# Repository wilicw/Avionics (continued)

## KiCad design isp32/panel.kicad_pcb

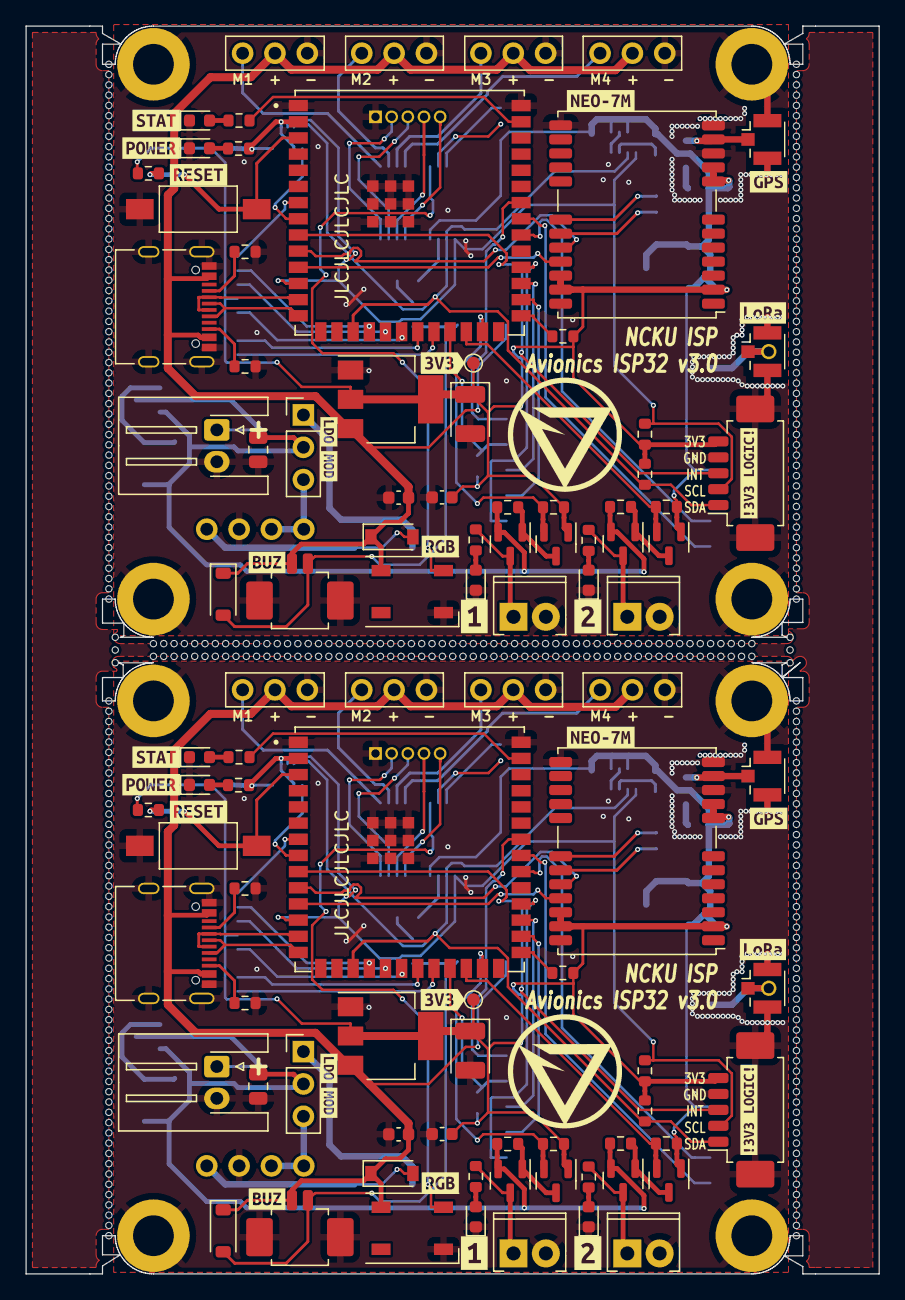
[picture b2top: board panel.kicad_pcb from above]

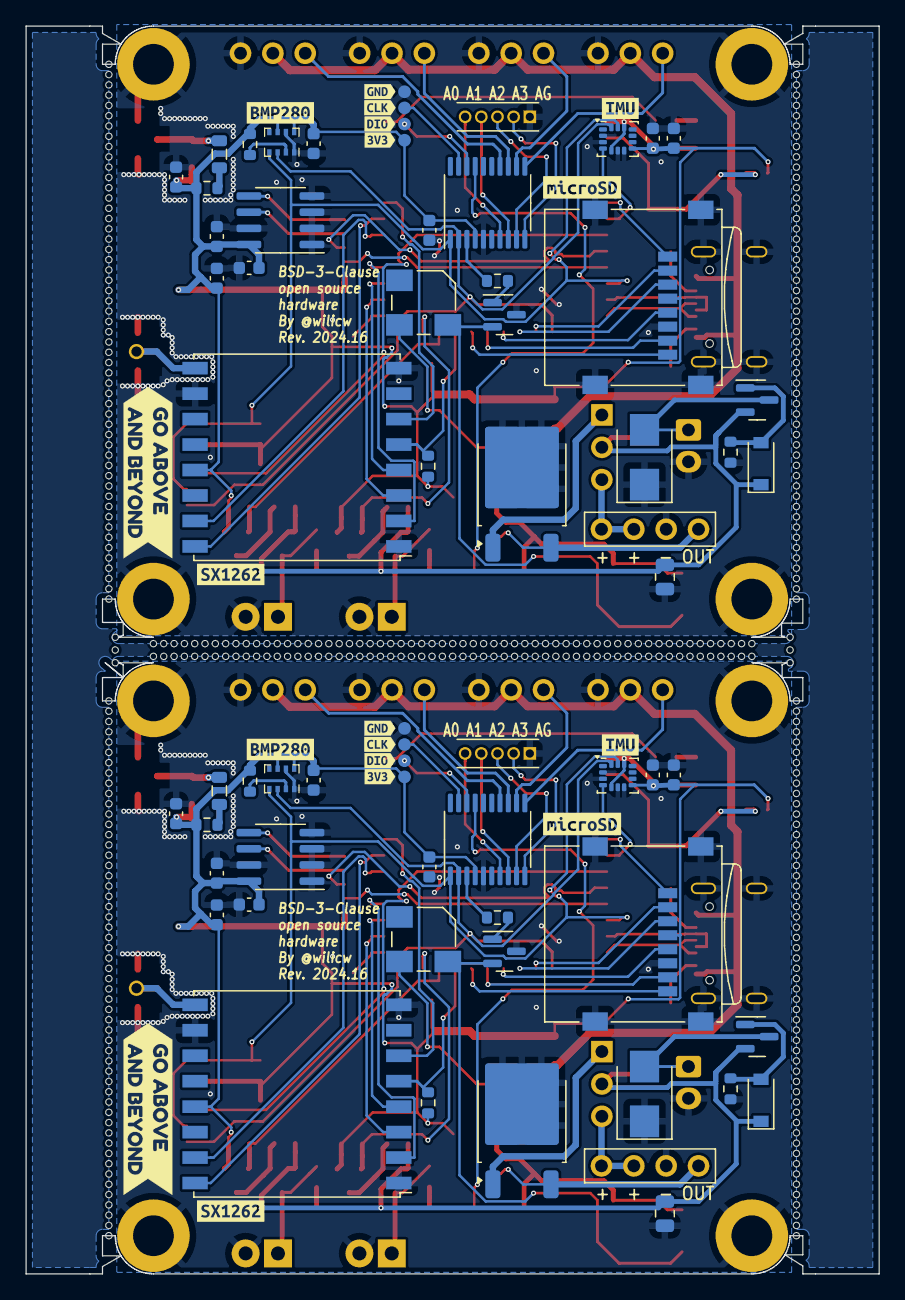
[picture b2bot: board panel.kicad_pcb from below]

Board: 2 copper layers, 67.0 x 98.0 mm, 552 parts (86 on the bottom side), 130 nets.

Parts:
C3, C3#2, C9, C9#2, C11, C11#2, C13, C13#2, C16, C16#2, C23, C23#2: 100n; C_0603_1608Metric
C5, C5#2: 100n; C_0805_2012Metric
C6, C6#2, C10, C10#2: 22u; C_0603_1608Metric
C12, C12#2: 220u; CP_EIA-3528-12_Kemet-T
C14, C14#2, C22, C22#2: 1u; C_0603_1608Metric
C15, C15#2: 10u; C_0805_2012Metric
D1, D1#2: Zener; D_SOD-123
D2, D2#2: F0_LED; LED_0603_1608Metric
D3, D3#2: ESP_LED; LED_0603_1608Metric
D4, D4#2: F1_LED; LED_0603_1608Metric
D5, D5#2: POWER; LED_0603_1608Metric
D6, D6#2: TVS; D_SMB
D7, D7#2: WS2812B; LED_WS2812B_PLCC4_5.0x5.0mm_P3.2mm
D8, D8#2: D_Shockley; D_SOD-123
D9, D9#2: D_Small; D_SOD-123
H1, H1#2, H2, H2#2, H3, H3#2, H4, H4#2: MountingHole_Pad; MountingHole_3.2mm_M3_ISO7380_Pad
J1, J1#2: BAT1; JST_XH_S2B-XH-A-1_1x02_P2.50mm_Horizontal
J2, J2#2: ExtBoard; Molex_PicoBlade_53261-0571_1x05-1MP_P1.25mm_Horizontal
J3, J3#2: USB_C_Receptacle_USB2.0; USB_C_Receptacle_Palconn_UTC16-G
J4, J4#2: ADC; PinHeader_1x05_P1.27mm_Vertical
J5, J5#2: GPS_ANT; U.FL_Hirose_U.FL-R-SMT-1_Vertical
J6, J6#2: F0; TerminalBlock_Phoenix_MPT-0,5-2-2.54_1x02_P2.54mm_Horizontal
J7, J7#2: F1; TerminalBlock_Phoenix_MPT-0,5-2-2.54_1x02_P2.54mm_Horizontal
J9, J9#2: ANT; PinHeader_1x01_P2.00mm_Vertical
J10, J10#2: LoRa_ANT; U.FL_Hirose_U.FL-R-SMT-1_Vertical
J11, J11#2: Power Modules; PinSocket_1x04_P2.54mm_Vertical
J12, J12#2: Micro_SD_Card; microSD_HC_Wuerth_693072010801
J13, J13#2: VIN_SELECT; PinHeader_1x03_P2.54mm_Vertical
J14, J14#2: BUZZ; Molex_PicoBlade_53261-0271_1x02-1MP_P1.25mm_Horizontal
KiKit_MB_1_1, KiKit_MB_1_2, KiKit_MB_1_3, KiKit_MB_1_4, KiKit_MB_1_5, KiKit_MB_1_6, KiKit_MB_1_7, KiKit_MB_1_8, KiKit_MB_1_9, KiKit_MB_1_10, KiKit_MB_1_11, KiKit_MB_1_12, KiKit_MB_1_13, KiKit_MB_1_14, KiKit_MB_1_15, KiKit_MB_1_16, KiKit_MB_1_17, KiKit_MB_1_18, KiKit_MB_1_19, KiKit_MB_1_20, KiKit_MB_1_21, KiKit_MB_1_22, KiKit_MB_1_23, KiKit_MB_1_24, KiKit_MB_1_25, KiKit_MB_1_26, KiKit_MB_1_27, KiKit_MB_1_28, KiKit_MB_1_29, KiKit_MB_1_30, KiKit_MB_1_31, KiKit_MB_1_32, KiKit_MB_1_33, KiKit_MB_1_34, KiKit_MB_1_35, KiKit_MB_1_36, KiKit_MB_1_37, KiKit_MB_1_38, KiKit_MB_1_39, KiKit_MB_1_40, KiKit_MB_1_41, KiKit_MB_1_42, KiKit_MB_1_43, KiKit_MB_1_44, KiKit_MB_1_45, KiKit_MB_1_46, KiKit_MB_1_47, KiKit_MB_1_48, KiKit_MB_1_49, KiKit_MB_1_50, KiKit_MB_1_51, KiKit_MB_1_52, KiKit_MB_1_53, KiKit_MB_2_1, KiKit_MB_2_2, KiKit_MB_2_3, KiKit_MB_2_4, KiKit_MB_2_5, KiKit_MB_2_6, KiKit_MB_2_7, KiKit_MB_2_8, KiKit_MB_2_9, KiKit_MB_2_10, KiKit_MB_2_11, KiKit_MB_2_12, KiKit_MB_2_13, KiKit_MB_2_14, KiKit_MB_2_15, KiKit_MB_2_16, KiKit_MB_2_17, KiKit_MB_2_18, KiKit_MB_2_19, KiKit_MB_2_20, KiKit_MB_2_21, KiKit_MB_2_22, KiKit_MB_2_23, KiKit_MB_2_24, KiKit_MB_2_25, KiKit_MB_2_26, KiKit_MB_2_27, KiKit_MB_2_28, KiKit_MB_2_29, KiKit_MB_2_30, KiKit_MB_2_31, KiKit_MB_2_32, KiKit_MB_2_33, KiKit_MB_2_34, KiKit_MB_2_35, KiKit_MB_2_36, KiKit_MB_2_37, KiKit_MB_2_38, KiKit_MB_2_39, KiKit_MB_2_40, KiKit_MB_2_41, KiKit_MB_2_42, KiKit_MB_2_43, KiKit_MB_2_44, KiKit_MB_2_45, KiKit_MB_2_46, KiKit_MB_2_47, KiKit_MB_2_48, KiKit_MB_2_49, KiKit_MB_2_50, KiKit_MB_2_51, KiKit_MB_2_52, KiKit_MB_2_53, KiKit_MB_2_54, KiKit_MB_2_55, KiKit_MB_2_56, KiKit_MB_2_57, KiKit_MB_2_58, KiKit_MB_2_59, KiKit_MB_3_1, KiKit_MB_3_2, KiKit_MB_3_3, KiKit_MB_3_4, KiKit_MB_3_5, KiKit_MB_3_6, KiKit_MB_3_7, KiKit_MB_3_8, KiKit_MB_3_9, KiKit_MB_3_10, KiKit_MB_3_11, KiKit_MB_3_12, KiKit_MB_3_13, KiKit_MB_3_14, KiKit_MB_3_15, KiKit_MB_3_16, KiKit_MB_3_17, KiKit_MB_3_18, KiKit_MB_3_19, KiKit_MB_3_20, KiKit_MB_3_21, KiKit_MB_3_22, KiKit_MB_3_23, KiKit_MB_3_24, KiKit_MB_3_25, KiKit_MB_3_26, KiKit_MB_3_27, KiKit_MB_3_28, KiKit_MB_3_29, KiKit_MB_3_30, KiKit_MB_3_31, KiKit_MB_3_32, KiKit_MB_3_33, KiKit_MB_3_34, KiKit_MB_3_35, KiKit_MB_3_36, KiKit_MB_3_37, KiKit_MB_3_38, KiKit_MB_3_39, KiKit_MB_3_40, KiKit_MB_3_41, KiKit_MB_3_42, KiKit_MB_3_43, KiKit_MB_3_44, KiKit_MB_3_45, KiKit_MB_3_46, KiKit_MB_3_47, KiKit_MB_3_48, KiKit_MB_3_49, KiKit_MB_3_50, KiKit_MB_3_51, KiKit_MB_3_52, KiKit_MB_3_53, KiKit_MB_4_1, KiKit_MB_4_2, KiKit_MB_4_3, KiKit_MB_4_4, KiKit_MB_4_5, KiKit_MB_4_6, KiKit_MB_4_7, KiKit_MB_4_8, KiKit_MB_4_9, KiKit_MB_4_10, KiKit_MB_4_11, KiKit_MB_4_12, KiKit_MB_4_13, KiKit_MB_4_14, KiKit_MB_4_15, KiKit_MB_4_16, KiKit_MB_4_17, KiKit_MB_4_18, KiKit_MB_4_19, KiKit_MB_4_20, KiKit_MB_4_21, KiKit_MB_4_22, KiKit_MB_4_23, KiKit_MB_4_24, KiKit_MB_4_25, KiKit_MB_4_26, KiKit_MB_4_27, KiKit_MB_4_28, KiKit_MB_4_29, KiKit_MB_4_30, KiKit_MB_4_31, KiKit_MB_4_32, KiKit_MB_4_33, KiKit_MB_4_34, KiKit_MB_4_35, KiKit_MB_4_36, KiKit_MB_4_37, KiKit_MB_4_38, KiKit_MB_4_39, KiKit_MB_4_40, KiKit_MB_4_41, KiKit_MB_4_42, KiKit_MB_4_43, KiKit_MB_4_44, KiKit_MB_4_45, KiKit_MB_4_46, KiKit_MB_4_47, KiKit_MB_4_48, KiKit_MB_4_49, KiKit_MB_4_50, KiKit_MB_4_51, KiKit_MB_4_52, KiKit_MB_4_53, KiKit_MB_5_1, KiKit_MB_5_2, KiKit_MB_5_3, KiKit_MB_5_4, KiKit_MB_5_5, KiKit_MB_5_6, KiKit_MB_5_7, KiKit_MB_5_8, KiKit_MB_5_9, KiKit_MB_5_10, KiKit_MB_5_11, KiKit_MB_5_12, KiKit_MB_5_13, KiKit_MB_5_14, KiKit_MB_5_15, KiKit_MB_5_16, KiKit_MB_5_17, KiKit_MB_5_18, KiKit_MB_5_19, KiKit_MB_5_20, KiKit_MB_5_21, KiKit_MB_5_22, KiKit_MB_5_23, KiKit_MB_5_24, KiKit_MB_5_25, KiKit_MB_5_26, KiKit_MB_5_27, KiKit_MB_5_28, KiKit_MB_5_29, KiKit_MB_5_30, KiKit_MB_5_31, KiKit_MB_5_32, KiKit_MB_5_33, KiKit_MB_5_34, KiKit_MB_5_35, KiKit_MB_5_36, KiKit_MB_5_37, KiKit_MB_5_38, KiKit_MB_5_39, KiKit_MB_5_40, KiKit_MB_5_41, KiKit_MB_5_42, KiKit_MB_5_43, KiKit_MB_5_44, KiKit_MB_5_45, KiKit_MB_5_46, KiKit_MB_5_47, KiKit_MB_5_48, KiKit_MB_5_49, KiKit_MB_5_50, KiKit_MB_5_51, KiKit_MB_5_52, KiKit_MB_5_53, KiKit_MB_5_54, KiKit_MB_5_55, KiKit_MB_5_56, KiKit_MB_5_57, KiKit_MB_5_58, KiKit_MB_5_59, KiKit_MB_6_1, KiKit_MB_6_2, KiKit_MB_6_3, KiKit_MB_6_4, KiKit_MB_6_5, KiKit_MB_6_6, KiKit_MB_6_7, KiKit_MB_6_8, KiKit_MB_6_9, KiKit_MB_6_10, KiKit_MB_6_11, KiKit_MB_6_12, KiKit_MB_6_13, KiKit_MB_6_14, KiKit_MB_6_15, KiKit_MB_6_16, KiKit_MB_6_17, KiKit_MB_6_18, KiKit_MB_6_19, KiKit_MB_6_20, KiKit_MB_6_21, KiKit_MB_6_22, KiKit_MB_6_23, KiKit_MB_6_24, KiKit_MB_6_25, KiKit_MB_6_26, KiKit_MB_6_27, KiKit_MB_6_28, KiKit_MB_6_29, KiKit_MB_6_30, KiKit_MB_6_31, KiKit_MB_6_32, KiKit_MB_6_33, KiKit_MB_6_34, KiKit_MB_6_35, KiKit_MB_6_36, KiKit_MB_6_37, KiKit_MB_6_38, KiKit_MB_6_39, KiKit_MB_6_40, KiKit_MB_6_41, KiKit_MB_6_42, KiKit_MB_6_43, KiKit_MB_6_44, KiKit_MB_6_45, KiKit_MB_6_46, KiKit_MB_6_47, KiKit_MB_6_48, KiKit_MB_6_49, KiKit_MB_6_50, KiKit_MB_6_51, KiKit_MB_6_52, KiKit_MB_6_53, KiKit_MB_7_1, KiKit_MB_7_2, KiKit_MB_7_3, KiKit_MB_8_1, KiKit_MB_8_2, KiKit_MB_8_3: NPTH
L2, L2#2: 22u; L_0805_2012Metric
LS1, LS1#2: 5020; XDCR_KSSG33J12-3
M1, M1#2, M2, M2#2, M3, M3#2, M4, M4#2: Motor_Servo; PinHeader_1x03_P2.54mm_Vertical
Q1, Q1#2, Q4, Q4#2: BSS138; SOT-23
Q2, Q2#2: S8050; SOT-23
Q3, Q3#2, Q5, Q5#2, Q6, Q6#2: IRLML6402; SOT-23
R1, R1#2, R2, R2#2, R14, R14#2, R15, R15#2, R22, R22#2, R25, R25#2: 10k; R_0603_1608Metric
R3, R3#2: 100; R_0603_1608Metric
R4, R4#2, R6, R6#2: 4k7; R_0603_1608Metric
R5, R5#2, R7, R7#2: 5k1; R_0603_1608Metric
R12, R12#2: 22; R_0603_1608Metric
R16, R16#2, R20, R20#2, R23, R23#2, R24, R24#2: 100K; R_0603_1608Metric
R18, R18#2, R19, R19#2: 1k; R_0603_1608Metric
R26, R26#2: 100k; R_0603_1608Metric
SW1, SW1#2: RST; SW_SPST_FSMSM
TP1, TP1#2: 3V3; TestPoint_Pad_D1.0mm
TP2, TP2#2: TP-3V3; TestPoint_Pad_D1.0mm
TP3, TP3#2: SWDIO; TestPoint_Pad_D1.0mm
TP4, TP4#2: SWCLK; TestPoint_Pad_D1.0mm
TP5, TP5#2: GND; TestPoint_Pad_D1.0mm
U1, U1#2: AZ1117-3.3; SOT-223-3_TabPin2
U2, U2#2: BA05C; TO-252-2
U3, U3#2: STM32G030F6; TSSOP-20_4.4x6.5mm_P0.65mm
U4, U4#2: LSM6DSM; LGA-14_3x2.5mm_P0.5mm_LayoutBorder3x4y
U6, U6#2: 24LC32; SOIC-8_3.9x4.9mm_P1.27mm
U7, U7#2: NEO-XM; ublox_NEO
U8, U8#2: ESP32-S3-WROOM-1U; XCVR_ESP32-S3-WROOM-1U
U9, U9#2: RFM98W-315S2; HOPERF_RFM9XW_SMD
U10, U10#2: BMP280; Bosch_LGA-8_2x2.5mm_P0.65mm_ClockwisePinNumbering
kibuzzard-63CD1E7F, kibuzzard-63CD1E7F#2: G***; kibuzzard-63CD1E7F
kibuzzard-63CD1E61, kibuzzard-63CD1E61#2: G***; kibuzzard-63CD1E61
kibuzzard-63CD1EC0, kibuzzard-63CD1EC0#2: G***; kibuzzard-63CD1EC0
kibuzzard-63CD1EC5, kibuzzard-63CD1EC5#2: G***; kibuzzard-63CD1EC5
kibuzzard-63CD04EB, kibuzzard-63CD04EB#2: G***; kibuzzard-63CD04EB
kibuzzard-63CD04FB, kibuzzard-63CD04FB#2: G***; kibuzzard-63CD04FB
kibuzzard-641A73AC, kibuzzard-641A73AC#2: G***; kibuzzard-641A73AC
kibuzzard-641A73E5, kibuzzard-641A73E5#2: G***; kibuzzard-641A73E5
kibuzzard-641A73FA, kibuzzard-641A73FA#2: G***; kibuzzard-641A73FA
kibuzzard-641A737F, kibuzzard-641A737F#2: G***; kibuzzard-641A737F
kibuzzard-641A7395, kibuzzard-641A7395#2: G***; kibuzzard-641A7395
kibuzzard-641A7704, kibuzzard-641A7704#2: G***; kibuzzard-641A7704
kibuzzard-642D97EE, kibuzzard-642D97EE#2: G***; kibuzzard-642D97EE
kibuzzard-661FABB5, kibuzzard-661FABB5#2: G***; kibuzzard-661FABB5
kibuzzard-661FAECF, kibuzzard-661FAECF#2: G***; kibuzzard-661FAECF
kibuzzard-661FBC0A, kibuzzard-661FBC0A#2: G***; kibuzzard-661FBC0A
kibuzzard-661FBC21, kibuzzard-661FBC21#2: G***; kibuzzard-661FBC21
kibuzzard-66439A83, kibuzzard-66439A83#2: G***; kibuzzard-66439A83
kibuzzard-66439ACD, kibuzzard-66439ACD#2: G***; kibuzzard-66439ACD
kibuzzard-66439AF0, kibuzzard-66439AF0#2: G***; kibuzzard-66439AF0
kibuzzard-66439B8F, kibuzzard-66439B8F#2: G***; kibuzzard-66439B8F
kibuzzard-66439B33, kibuzzard-66439B33#2: G***; kibuzzard-66439B33
kibuzzard-66439C31, kibuzzard-66439C31#2: G***; kibuzzard-66439C31

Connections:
Board_0-+3V3: C3#2.1, C9.1, C10#2.1, C11.1, C12#2.1, C13#2.1, C14.1, C16.1, C22#2.1, C23.1, J2#2.5, J12#2.4 (VDD), Q1#2.1 (G), Q4#2.1 (G), R1.1, R2#2.1, R4#2.1, R6.1, R12.1, R14#2.1, R15.1, R16#2.1, R18#2.1, R23#2.1, TP1#2.1, TP2#2.1, U1#2.2 (VO), U3#2.4 (VDD), U4#2.5 (VDDIO), U4#2.8 (VDD), U4#2.12 (CS), U6.8 (VCC), U7.2 (D_SEL), U7.8 (~RESET), U7.9 (VCC_RF), U7.22 (V_BCKP), U7.23 (VCC), U8.2 (3V3), U9#2.13 (3.3V), U10#2.6 (VDDIO), U10#2.8 (VDD)
Board_0-+5V: C6.1, D7.1 (VDD), D8.1 (K), D9.1 (K), J3#2.A4 (VBUS), J3#2.A9 (VBUS), J3#2.B4 (VBUS), J3#2.B9 (VBUS), J14.1, LS1#2.P, M1#2.2 (+), M2#2.2 (+), M3#2.2 (+), M4.2 (+), U1#2.3 (VI)
Board_0-+BATT: C5.1, C15#2.1, D1.1 (K), J13#2.2, Q3.2 (S), Q5.2 (S), Q6#2.2 (S), R20#2.1, R24#2.1
Board_0-ADC0: J4#2.1, U3#2.7 (PA0)
Board_0-ADC1: J4#2.2, U3#2.8 (PA1)
Board_0-ADC2: J4#2.3, U3#2.9 (PA2)
Board_0-ADC3: J4#2.4, U3#2.10 (PA3)
Board_0-Buzz: R3#2.1, U3#2.3 (PC15-OSC32_OUT)
Board_0-D+: J3#2.A6 (D+), J3#2.B6 (D+), U8.14 (IO20)
Board_0-D-: J3#2.A7 (D-), J3#2.B7 (D-), U8.13 (IO19)
Board_0-EXT_INT: J2#2.3, U8.9 (IO16)
Board_0-FIRE0: Q1#2.2 (S), R16#2.2, U8.24 (IO47)
Board_0-FIRE1: Q4#2.2 (S), R23#2.2, U8.25 (IO48)
Board_0-GND: C3#2.2, C5.2, C6.2, C9.2, C10#2.2, C11.2, C12#2.2, C13#2.2, C14.2, C15#2.2, C16.2, C22#2.2, C23.2, D2.1 (K), D3#2.1 (K), D4#2.1 (K), D5.1 (K), D6#2.1 (A1), D7.3 (VSS), H1#2.1, H2.1, H3#2.1, H4#2.1, J1#2.2, J2#2.4, J2#2.MP (MountPin), J3#2.A1 (GND), J3#2.A12 (GND), J3#2.B1 (GND), J3#2.B12 (GND), J3#2.S1 (SHIELD), J4#2.5, J5.2 (Ext), J6.2, J7.2, J10.2 (Ext), J11.2, J12#2.6 (VSS), J12#2.9 (SHIELD), J14.MP (MountPin), M1#2.3 (-), M2#2.3 (-), M3#2.3 (-), M4.3 (-), Q2#2.3 (E), R5.2, R7.2, R26.2, SW1.1, TP5#2.1, U1#2.1 (GND), U2#2.2 (GND), U3#2.5 (VSS), U4#2.2 (SDX), U4#2.3 (SCX), U4#2.6 (GND), U4#2.7 (GND), U6.1 (A0), U6.2 (A1), U6.3 (A2), U6.4 (GND), U6.7 (WP), U7.10 (GND), U7.12 (GND), U7.13 (GND), U7.24 (GND), U8.1 (GND), U8.40 (GND), U8.41_1 (GND), U8.41_2 (GND), U8.41_3 (GND), U8.41_4 (GND), U8.41_5 (GND), U8.41_6 (GND), U8.41_7 (GND), U8.41_8 (GND), U8.41_9 (GND), U9#2.1 (GND), U9#2.8 (GND), U9#2.10 (GND), U10#2.1 (GND), U10#2.7 (GND)
Board_0-IMU_INT: U4#2.4 (INT1), U8.8 (IO15)
Board_0-INDI: R19.1, U8.39 (IO1)
Board_0-IO0: R2#2.2, U8.27 (IO0)
Board_0-LORA_BUSY: U8.33 (IO40), U9#2.16 (DIO2)
Board_0-LORA_D1: U8.32 (IO39), U9#2.15 (DIO1)
Board_0-LORA_RST: U8.34 (IO41), U9#2.6 (RESET)
Board_0-LORA_SS: R15.2, U8.23 (IO21), U9#2.5 (NSS)
Board_0-MISO_1: U8.30 (IO37), U9#2.2 (MISO)
Board_0-MOSI_1: U8.28 (IO35), U9#2.3 (MOSI)
Board_0-Net-(D1-A): D1.2 (A), Q6#2.1 (G), R26.1
Board_0-Net-(D2-A): D2.2 (A), R22#2.1
Board_0-Net-(D3-A): D3#2.2 (A), R19.2
Board_0-Net-(D4-A): D4#2.2 (A), R25#2.1
Board_0-Net-(D5-A): D5.2 (A), R18#2.2
Board_0-Net-(D6-A2): D6#2.2 (A2), J1#2.1, Q6#2.3 (D)
Board_0-Net-(D8-A): D8.2 (A), J11.1, U2#2.3 (VOUT)
Board_0-Net-(D9-A): D9.2 (A), J14.2, LS1#2.N, Q2#2.2 (C)
Board_0-Net-(J5-In): J5.1 (In), L2#2.2, U7.11 (RF_IN)
Board_0-Net-(J6-Pin_1): J6.1, Q3.3 (D), R22#2.2
Board_0-Net-(J7-Pin_1): J7.1, Q5.3 (D), R25#2.2
Board_0-Net-(J10-In): J9#2.1, J10.1 (In), U9#2.9 (ANT)
Board_0-Net-(J11-Pin_3): J11.3, J11.4, J13#2.3
Board_0-Net-(J13-Pin_1): J13#2.1, U2#2.1 (VIN)
Board_0-Net-(L2-Pad1): L2#2.1, R12.2
Board_0-Net-(Q1-D): Q1#2.3 (D), Q3.1 (G), R20#2.2
Board_0-Net-(Q2-B): Q2#2.1 (B), R3#2.2
Board_0-Net-(Q4-D): Q4#2.3 (D), Q5.1 (G), R24#2.2
Board_0-Net-(U6-SCL): U6.6 (SCL), U7.19 (SCL/SPI_CLK)
Board_0-Net-(U6-SDA): U6.5 (SDA), U7.18 (SDA/~SPI_CS)
Board_0-Net-(U10-CSB): R14#2.2, U10#2.2 (CSB)
Board_0-RGB: D7.4 (DIN), U3#2.17 (PA12[PA10])
Board_0-RST: R1.2, SW1.2, U8.3 (EN)
Board_0-RX1: U7.20 (TXD/SPI_MISO), U8.10 (IO17)
Board_0-SCK_1: U8.29 (IO36), U9#2.4 (SCK)
Board_0-SCL: J2#2.2, R6.2, U3#2.1 (PB7/PB8), U4#2.13 (SCL), U8.12 (IO8), U10#2.4 (SCK)
Board_0-SDA: J2#2.1, R4#2.2, U3#2.2 (PB9/PC14-OSC32_IN), U4#2.14 (SDA), U8.17 (IO9), U10#2.3 (SDI)
Board_0-SD_CLK: J12#2.5 (CLK), U8.20 (IO12)
Board_0-SD_CMD: J12#2.3 (CMD), U8.19 (IO11)
Board_0-SD_D0: J12#2.7 (DAT0), U8.21 (IO13)
Board_0-SD_D1: J12#2.8 (DAT1), U8.22 (IO14)
Board_0-SD_D2: J12#2.1 (DAT2), U8.7 (IO7)
Board_0-SD_D3: J12#2.2 (DAT3/CD), U8.18 (IO10)
Board_0-SERVO0: M1#2.1 (PWM), U3#2.11 (PA4)
Board_0-SERVO1: M2#2.1 (PWM), U3#2.12 (PA5)
Board_0-SERVO2: M3#2.1 (PWM), U3#2.13 (PA6)
Board_0-SERVO3: M4.1 (PWM), U3#2.14 (PA7)
Board_0-SWCLK: TP4#2.1, U3#2.19 (PA15/PA14-BOOT0)
Board_0-SWDIO: TP3#2.1, U3#2.18 (PA13)
Board_0-TX1: U7.21 (RXD/SPI_MOSI), U8.11 (IO18)
Board_0-cc1: J3#2.A5 (CC1), R5.1
Board_0-cc2: J3#2.B5 (CC2), R7.1
Board_1-+3V3: C3.1, C9#2.1, C10.1, C11#2.1, C12.1, C13.1, C14#2.1, C16#2.1, C22.1, C23#2.1, J2.5, J12.4 (VDD), Q1.1 (G), Q4.1 (G), R1#2.1, R2.1, R4.1, R6#2.1, R12#2.1, R14.1, R15#2.1, R16.1, R18.1, R23.1, TP1.1, TP2.1, U1.2 (VO), U3.4 (VDD), U4.5 (VDDIO), U4.8 (VDD), U4.12 (CS), U6#2.8 (VCC), U7#2.2 (D_SEL), U7#2.8 (~RESET), U7#2.9 (VCC_RF), U7#2.22 (V_BCKP), U7#2.23 (VCC), U8#2.2 (3V3), U9.13 (3.3V), U10.6 (VDDIO), U10.8 (VDD)
Board_1-+5V: C6#2.1, D7#2.1 (VDD), D8#2.1 (K), D9#2.1 (K), J3.A4 (VBUS), J3.A9 (VBUS), J3.B4 (VBUS), J3.B9 (VBUS), J14#2.1, LS1.P, M1.2 (+), M2.2 (+), M3.2 (+), M4#2.2 (+), U1.3 (VI)
Board_1-+BATT: C5#2.1, C15.1, D1#2.1 (K), J13.2, Q3#2.2 (S), Q5#2.2 (S), Q6.2 (S), R20.1, R24.1
Board_1-ADC0: J4.1, U3.7 (PA0)
Board_1-ADC1: J4.2, U3.8 (PA1)
Board_1-ADC2: J4.3, U3.9 (PA2)
Board_1-ADC3: J4.4, U3.10 (PA3)
Board_1-Buzz: R3.1, U3.3 (PC15-OSC32_OUT)
Board_1-D+: J3.A6 (D+), J3.B6 (D+), U8#2.14 (IO20)
Board_1-D-: J3.A7 (D-), J3.B7 (D-), U8#2.13 (IO19)
Board_1-EXT_INT: J2.3, U8#2.9 (IO16)
Board_1-FIRE0: Q1.2 (S), R16.2, U8#2.24 (IO47)
Board_1-FIRE1: Q4.2 (S), R23.2, U8#2.25 (IO48)
Board_1-GND: C3.2, C5#2.2, C6#2.2, C9#2.2, C10.2, C11#2.2, C12.2, C13.2, C14#2.2, C15.2, C16#2.2, C22.2, C23#2.2, D2#2.1 (K), D3.1 (K), D4.1 (K), D5#2.1 (K), D6.1 (A1), D7#2.3 (VSS), H1.1, H2#2.1, H3.1, H4.1, J1.2, J2.4, J2.MP (MountPin), J3.A1 (GND), J3.A12 (GND), J3.B1 (GND), J3.B12 (GND), J3.S1 (SHIELD), J4.5, J5#2.2 (Ext), J6#2.2, J7#2.2, J10#2.2 (Ext), J11#2.2, J12.6 (VSS), J12.9 (SHIELD), J14#2.MP (MountPin), M1.3 (-), M2.3 (-), M3.3 (-), M4#2.3 (-), Q2.3 (E), R5#2.2, R7#2.2, R26#2.2, SW1#2.1, TP5.1, U1.1 (GND), U2.2 (GND), U3.5 (VSS), U4.2 (SDX), U4.3 (SCX), U4.6 (GND), U4.7 (GND), U6#2.1 (A0), U6#2.2 (A1), U6#2.3 (A2), U6#2.4 (GND), U6#2.7 (WP), U7#2.10 (GND), U7#2.12 (GND), U7#2.13 (GND), U7#2.24 (GND), U8#2.1 (GND), U8#2.40 (GND), U8#2.41_1 (GND), U8#2.41_2 (GND), U8#2.41_3 (GND), U8#2.41_4 (GND), U8#2.41_5 (GND), U8#2.41_6 (GND), U8#2.41_7 (GND), U8#2.41_8 (GND), U8#2.41_9 (GND), U9.1 (GND), U9.8 (GND), U9.10 (GND), U10.1 (GND), U10.7 (GND)
Board_1-IMU_INT: U4.4 (INT1), U8#2.8 (IO15)
Board_1-INDI: R19#2.1, U8#2.39 (IO1)
Board_1-IO0: R2.2, U8#2.27 (IO0)
Board_1-LORA_BUSY: U8#2.33 (IO40), U9.16 (DIO2)
Board_1-LORA_D1: U8#2.32 (IO39), U9.15 (DIO1)
Board_1-LORA_RST: U8#2.34 (IO41), U9.6 (RESET)
Board_1-LORA_SS: R15#2.2, U8#2.23 (IO21), U9.5 (NSS)
Board_1-MISO_1: U8#2.30 (IO37), U9.2 (MISO)
Board_1-MOSI_1: U8#2.28 (IO35), U9.3 (MOSI)
Board_1-Net-(D1-A): D1#2.2 (A), Q6.1 (G), R26#2.1
Board_1-Net-(D2-A): D2#2.2 (A), R22.1
Board_1-Net-(D3-A): D3.2 (A), R19#2.2
Board_1-Net-(D4-A): D4.2 (A), R25.1
Board_1-Net-(D5-A): D5#2.2 (A), R18.2
Board_1-Net-(D6-A2): D6.2 (A2), J1.1, Q6.3 (D)
Board_1-Net-(D8-A): D8#2.2 (A), J11#2.1, U2.3 (VOUT)
Board_1-Net-(D9-A): D9#2.2 (A), J14#2.2, LS1.N, Q2.2 (C)
Board_1-Net-(J5-In): J5#2.1 (In), L2.2, U7#2.11 (RF_IN)
Board_1-Net-(J6-Pin_1): J6#2.1, Q3#2.3 (D), R22.2
Board_1-Net-(J7-Pin_1): J7#2.1, Q5#2.3 (D), R25.2
Board_1-Net-(J10-In): J9.1, J10#2.1 (In), U9.9 (ANT)
Board_1-Net-(J11-Pin_3): J11#2.3, J11#2.4, J13.3
Board_1-Net-(J13-Pin_1): J13.1, U2.1 (VIN)
Board_1-Net-(L2-Pad1): L2.1, R12#2.2
Board_1-Net-(Q1-D): Q1.3 (D), Q3#2.1 (G), R20.2
Board_1-Net-(Q2-B): Q2.1 (B), R3.2
Board_1-Net-(Q4-D): Q4.3 (D), Q5#2.1 (G), R24.2
Board_1-Net-(U6-SCL): U6#2.6 (SCL), U7#2.19 (SCL/SPI_CLK)
Board_1-Net-(U6-SDA): U6#2.5 (SDA), U7#2.18 (SDA/~SPI_CS)
Board_1-Net-(U10-CSB): R14.2, U10.2 (CSB)
Board_1-RGB: D7#2.4 (DIN), U3.17 (PA12[PA10])
Board_1-RST: R1#2.2, SW1#2.2, U8#2.3 (EN)
Board_1-RX1: U7#2.20 (TXD/SPI_MISO), U8#2.10 (IO17)
Board_1-SCK_1: U8#2.29 (IO36), U9.4 (SCK)
Board_1-SCL: J2.2, R6#2.2, U3.1 (PB7/PB8), U4.13 (SCL), U8#2.12 (IO8), U10.4 (SCK)
Board_1-SDA: J2.1, R4.2, U3.2 (PB9/PC14-OSC32_IN), U4.14 (SDA), U8#2.17 (IO9), U10.3 (SDI)
Board_1-SD_CLK: J12.5 (CLK), U8#2.20 (IO12)
Board_1-SD_CMD: J12.3 (CMD), U8#2.19 (IO11)
Board_1-SD_D0: J12.7 (DAT0), U8#2.21 (IO13)
Board_1-SD_D1: J12.8 (DAT1), U8#2.22 (IO14)
Board_1-SD_D2: J12.1 (DAT2), U8#2.7 (IO7)
Board_1-SD_D3: J12.2 (DAT3/CD), U8#2.18 (IO10)
Board_1-SERVO0: M1.1 (PWM), U3.11 (PA4)
Board_1-SERVO1: M2.1 (PWM), U3.12 (PA5)
Board_1-SERVO2: M3.1 (PWM), U3.13 (PA6)
Board_1-SERVO3: M4#2.1 (PWM), U3.14 (PA7)
Board_1-SWCLK: TP4.1, U3.19 (PA15/PA14-BOOT0)
Board_1-SWDIO: TP3.1, U3.18 (PA13)
Board_1-TX1: U7#2.21 (RXD/SPI_MOSI), U8#2.11 (IO18)
Board_1-cc1: J3.A5 (CC1), R5#2.1
Board_1-cc2: J3.B5 (CC2), R7#2.1

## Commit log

2022-12-03 feat: create a new platformio project
    Platformio project with vim environment and makefile
2022-12-03 feat: add githooks
2022-12-03 docs: add license and readme files
2022-12-04 feat: implement a simple state machine
2022-12-04 feat(indicator): add fastled library
2023-01-18 Update LICENSE
2024-04-17 feat: isp32 fix bugs
2024-04-18 chore: export pdf
2024-05-03 feat: re-design schematics
2024-07-25 chore: update isp32 project files
